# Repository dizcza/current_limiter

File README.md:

# Current Limiting circuit

See https://forum.allaboutcircuits.com/threads/how-to-build-a-current-limiting-circuit.146501/.

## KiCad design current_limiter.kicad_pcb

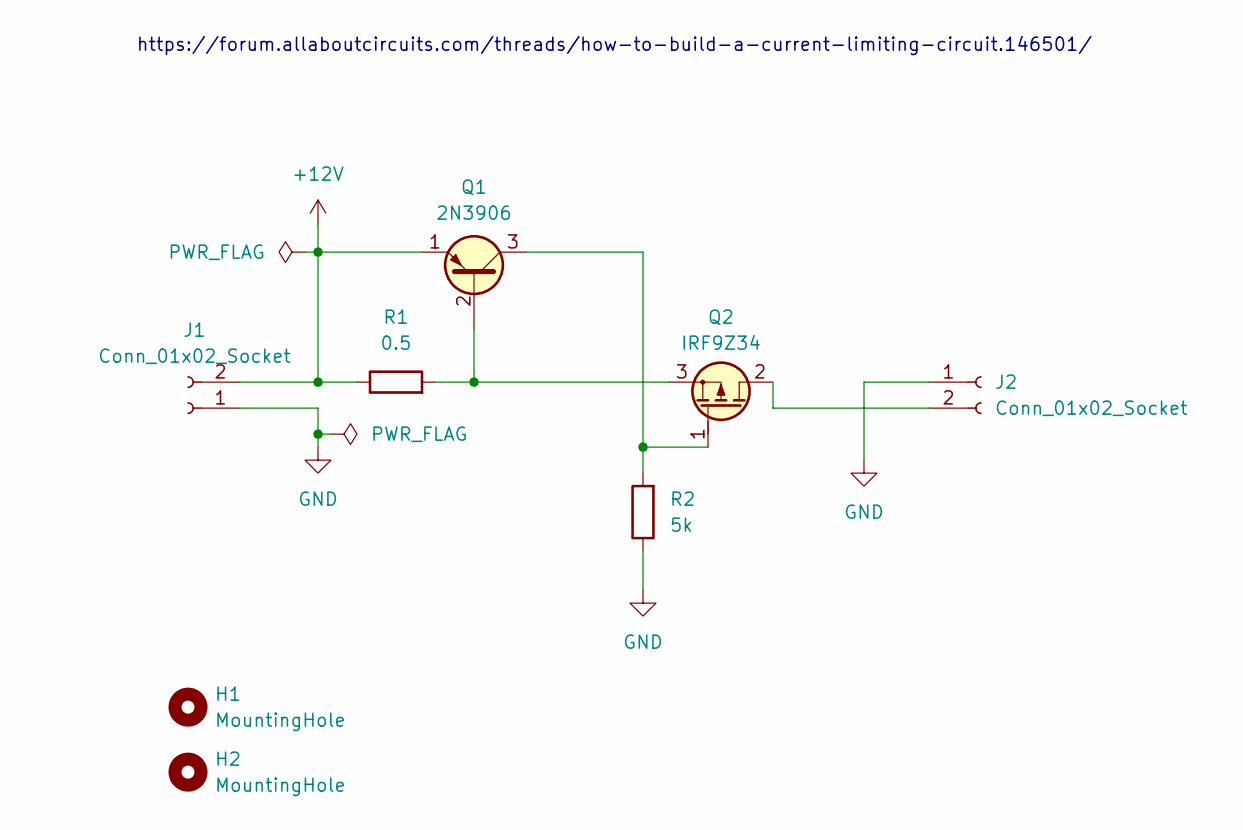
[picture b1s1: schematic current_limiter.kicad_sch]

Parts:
H1, H2: MountingHole; MountingHole_2.7mm_M2.5
J1, J2: Conn_01x02_Socket; JST_XH_S2B-XH-A-1_1x02_P2.50mm_Horizontal
Q1: 2N3906; TO-92_Inline_Wide_EBC
Q2: IRF9Z34; TO-220-3_Vertical_GDS
R1: 0.5; R_Axial_Power_L25.0mm_W6.4mm_P30.48mm
R2: 5k; R_Axial_DIN0207_L6.3mm_D2.5mm_P7.62mm_Horizontal

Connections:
+12V: J1.2, Q1.1 (E), R1.1
GND: J1.1, J2.1, R2.1
unnamed: J2.2, Q2.2 (D)
unnamed: Q1.2 (B), Q2.3 (S), R1.2
unnamed: Q1.3 (C), Q2.1 (G), R2.2

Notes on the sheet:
https://forum.allaboutcircuits.com/threads/how-to-build-a-current-limiting-circuit.146501/

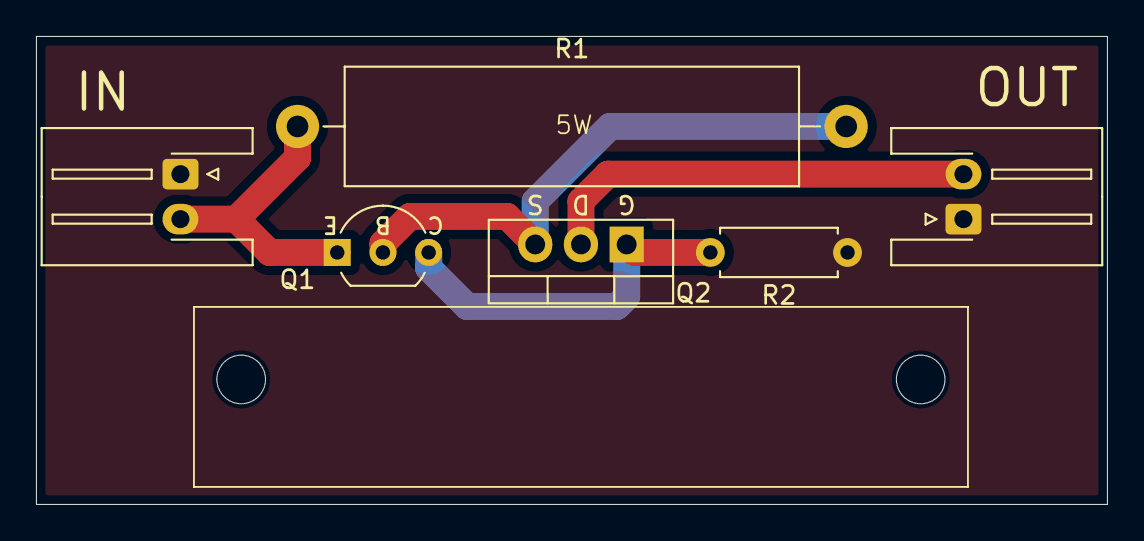
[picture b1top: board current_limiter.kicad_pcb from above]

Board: 2 copper layers, 59.5 x 26.0 mm, 8 parts (0 on the bottom side), 5 nets.

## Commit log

2024-11-13 v0.1
